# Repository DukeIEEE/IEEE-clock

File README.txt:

Analog LED clock

This is a project to create a programmable clock using LEDs to represent numbers and hand movements.

Contents:

AnalogClock - Arduino code
Designs - Clock designs for laser cutting
Schematics - PCB schematics and boards
Proposal - Contains a timeline for this workshop
Documents - Contains BOM and datasheets

Programming using arduino-1.0.1 and Arduino UNO programmer:

Place atmega into programmer
Connect all wires except reset to PCB
Upload ArduinoISP -- UNO, Arduino as ISP
Burn bootloader -- Arduino328, Arduino as ISP

Remove atmega from programmer
Connect reset wire
Run a sketch -- Arduino328, AVRISP mkII

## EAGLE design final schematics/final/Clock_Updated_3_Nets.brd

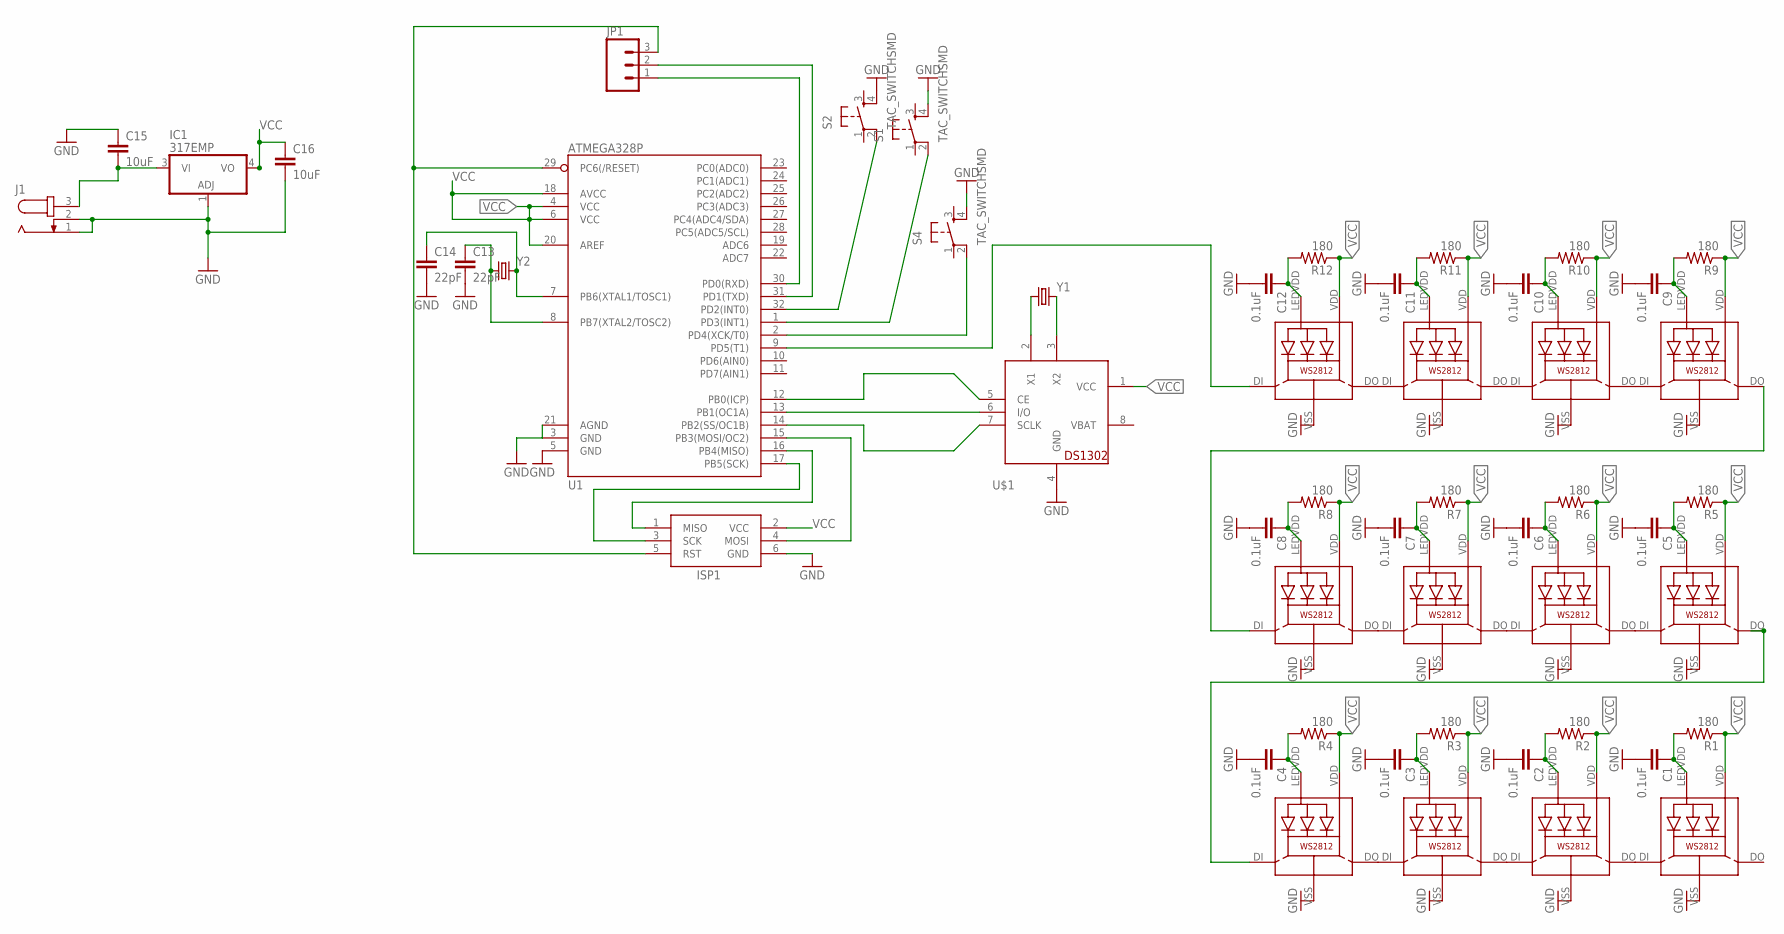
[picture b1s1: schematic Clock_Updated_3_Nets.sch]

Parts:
C1, C2, C3, C4, C5, C6, C7, C8, C9, C10, C11, C12: 0.1uF; 0603-CAP
C13, C14: 22pF; 0603-CAP
C15, C16: 10uF; 1206
IC1: 317EMP; SOT223
ISP1: AVRISP-6; AVRISP
J1: JACK-PLUG0; SPC4077
JP1: M03JST-PTH-VERT; JST-3-PTH-VERT
LED1, LED2, LED3, LED4, LED5, LED6, LED7, LED8, LED9, LED10, LED11, LED12: WS2812
R1, R2, R3, R4, R5, R6, R7, R8, R9, R10, R11, R12: 180; 0603-RES
S1, S2, S4: TAC_SWITCHSMD; TACTILE-SWITCH-SMD
U1: ATMEGA328P; TQFP32-08
U$1: DS1302; DIL08-ROUND
Y1: CRYSTALTC38H; TC38H
Y2: CRYSTALSMD; HC49UP

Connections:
GND: C1.2, C2.2, C3.2, C4.2, C5.2, C6.2, C7.2, C8.2, C9.2, C10.2, C11.2, C12.2, C13.2, C14.2, C15.1, C16.2, IC1.1 (ADJ), ISP1.6 (GND), J1.1, J1.2, LED1.VSS (GND), LED2.VSS (GND), LED3.VSS (GND), LED4.VSS (GND), LED5.VSS (GND), LED6.VSS (GND), LED7.VSS (GND), LED8.VSS (GND), LED9.VSS (GND), LED10.VSS (GND), LED11.VSS (GND), LED12.VSS (GND), S1.4, S2.4, S4.4, U1.3 (GND), U1.5 (GND), U1.21 (AGND), U$1.4 (GND)
unnamed: ISP1.4 (MOSI), U1.15 (PB3(MOSI/OC2))
unnamed: ISP1.1 (MISO), U1.16 (PB4(MISO))
unnamed: JP1.1, U1.30 (PD0(RXD))
unnamed: S2.2, U1.32 (PD2(INT0))
unnamed: U$1.3 (X2), Y1.2
unnamed: U$1.2 (X1), Y1.1
unnamed: C1.1, LED1.LEDVDD, R1.2
unnamed: C2.1, LED2.LEDVDD, R2.2
unnamed: LED1.DI, LED2.DO
unnamed: C3.1, LED3.LEDVDD, R3.2
unnamed: C4.1, LED4.LEDVDD, R4.2
unnamed: LED3.DI, LED4.DO
unnamed: C5.1, LED5.LEDVDD, R5.2
unnamed: C6.1, LED6.LEDVDD, R6.2
unnamed: LED5.DI, LED6.DO
unnamed: C7.1, LED7.LEDVDD, R7.2
unnamed: C8.1, LED8.LEDVDD, R8.2
unnamed: LED7.DI, LED8.DO
unnamed: C9.1, LED9.LEDVDD, R9.2
unnamed: C10.1, LED10.LEDVDD, R10.2
unnamed: LED9.DI, LED10.DO
unnamed: C11.1, LED11.LEDVDD, R11.2
unnamed: C12.1, LED12.LEDVDD, R12.2
unnamed: LED11.DI, LED12.DO
unnamed: LED4.DI, LED5.DO
unnamed: LED8.DI, LED9.DO
unnamed: JP1.2, U1.31 (PD1(TXD))
unnamed: S1.2, U1.1 (PD3(INT1))
unnamed: U1.13 (PB1(OC1A)), U$1.6 (I/O)
unnamed: U1.12 (PB0(ICP)), U$1.5 (CE)
unnamed: U1.14 (PB2(SS/OC1B)), U$1.7 (SCLK)
unnamed: ISP1.3 (SCK), U1.17 (PB5(SCK))
unnamed: ISP1.5 (RST), JP1.3, U1.29 (PC6(/RESET))
unnamed: S4.2, U1.2 (PD4(XCK/T0))
unnamed: C13.1, U1.8 (PB7(XTAL2/TOSC2)), Y2.1
unnamed: LED2.DI, LED3.DO
unnamed: LED6.DI, LED7.DO
unnamed: LED10.DI, LED11.DO
unnamed: LED12.DI, U1.9 (PD5(T1))
unnamed: C14.1, U1.7 (PB6(XTAL1/TOSC1)), Y2.2
unnamed: C15.2, IC1.3 (VI), J1.3
VBAT: U$1.8 (VBAT)
VCC: C16.1, IC1.4 (VO), ISP1.2 (VCC), LED1.VDD, LED2.VDD, LED3.VDD, LED4.VDD, LED5.VDD, LED6.VDD, LED7.VDD, LED8.VDD, LED9.VDD, LED10.VDD, LED11.VDD, LED12.VDD, R1.1, R2.1, R3.1, R4.1, R5.1, R6.1, R7.1, R8.1, R9.1, R10.1, R11.1, R12.1, U1.4 (VCC), U1.6 (VCC), U1.18 (AVCC), U1.20 (AREF), U$1.1 (VCC)

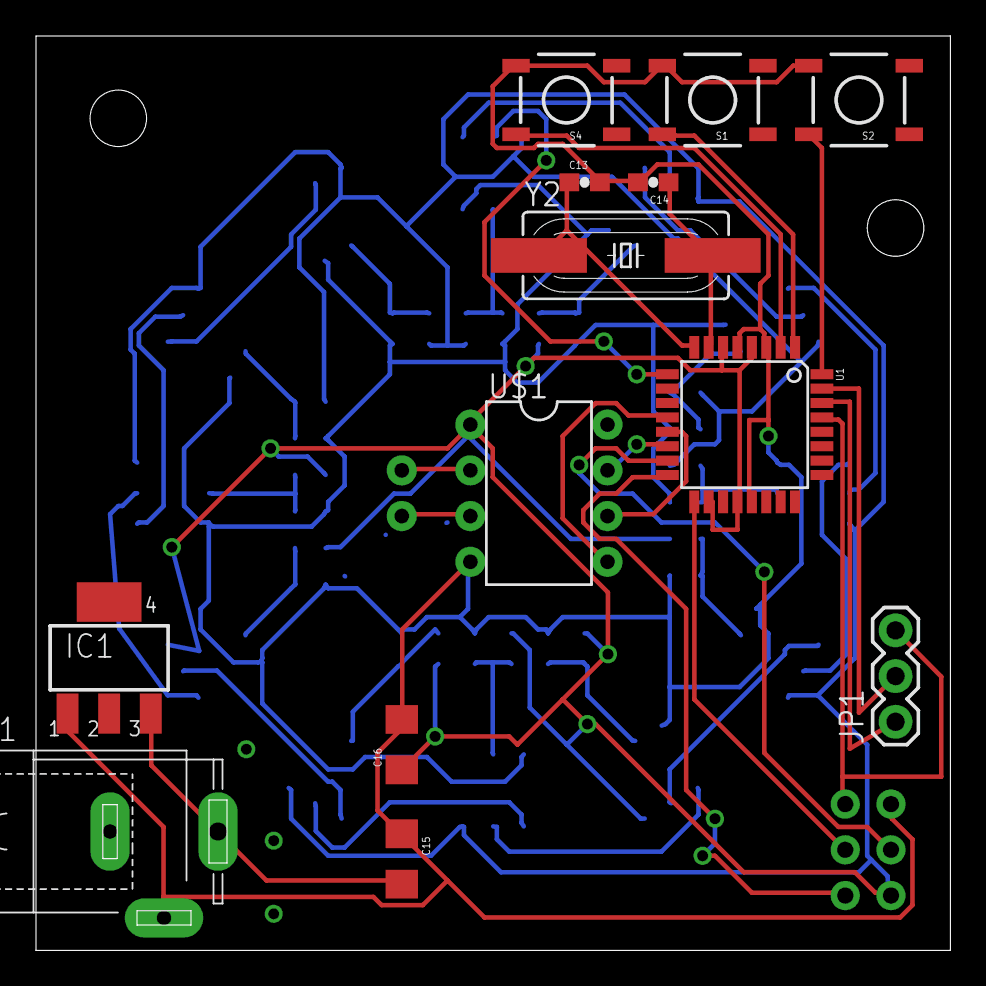
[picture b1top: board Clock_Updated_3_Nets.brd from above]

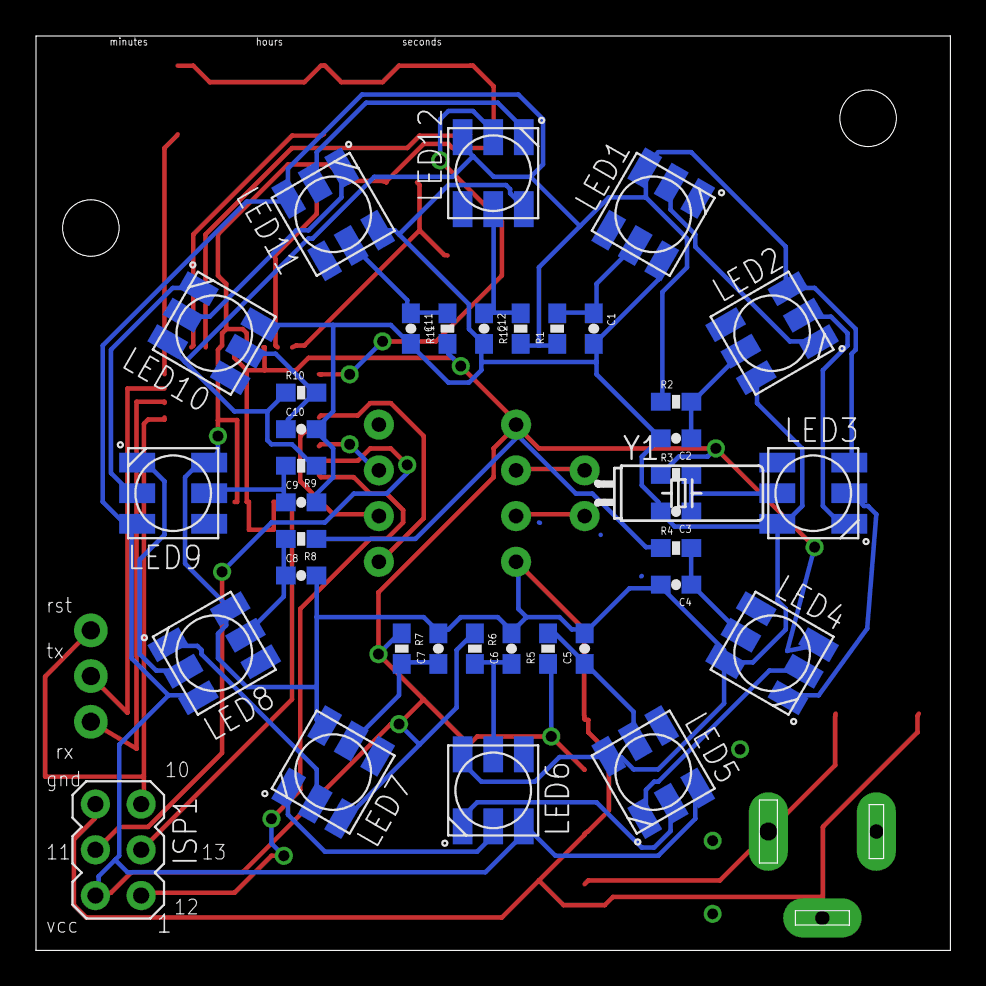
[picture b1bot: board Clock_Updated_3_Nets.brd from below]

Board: 2 copper layers, 50.8 x 50.8 mm, 51 parts (38 on the bottom side), 43 nets.

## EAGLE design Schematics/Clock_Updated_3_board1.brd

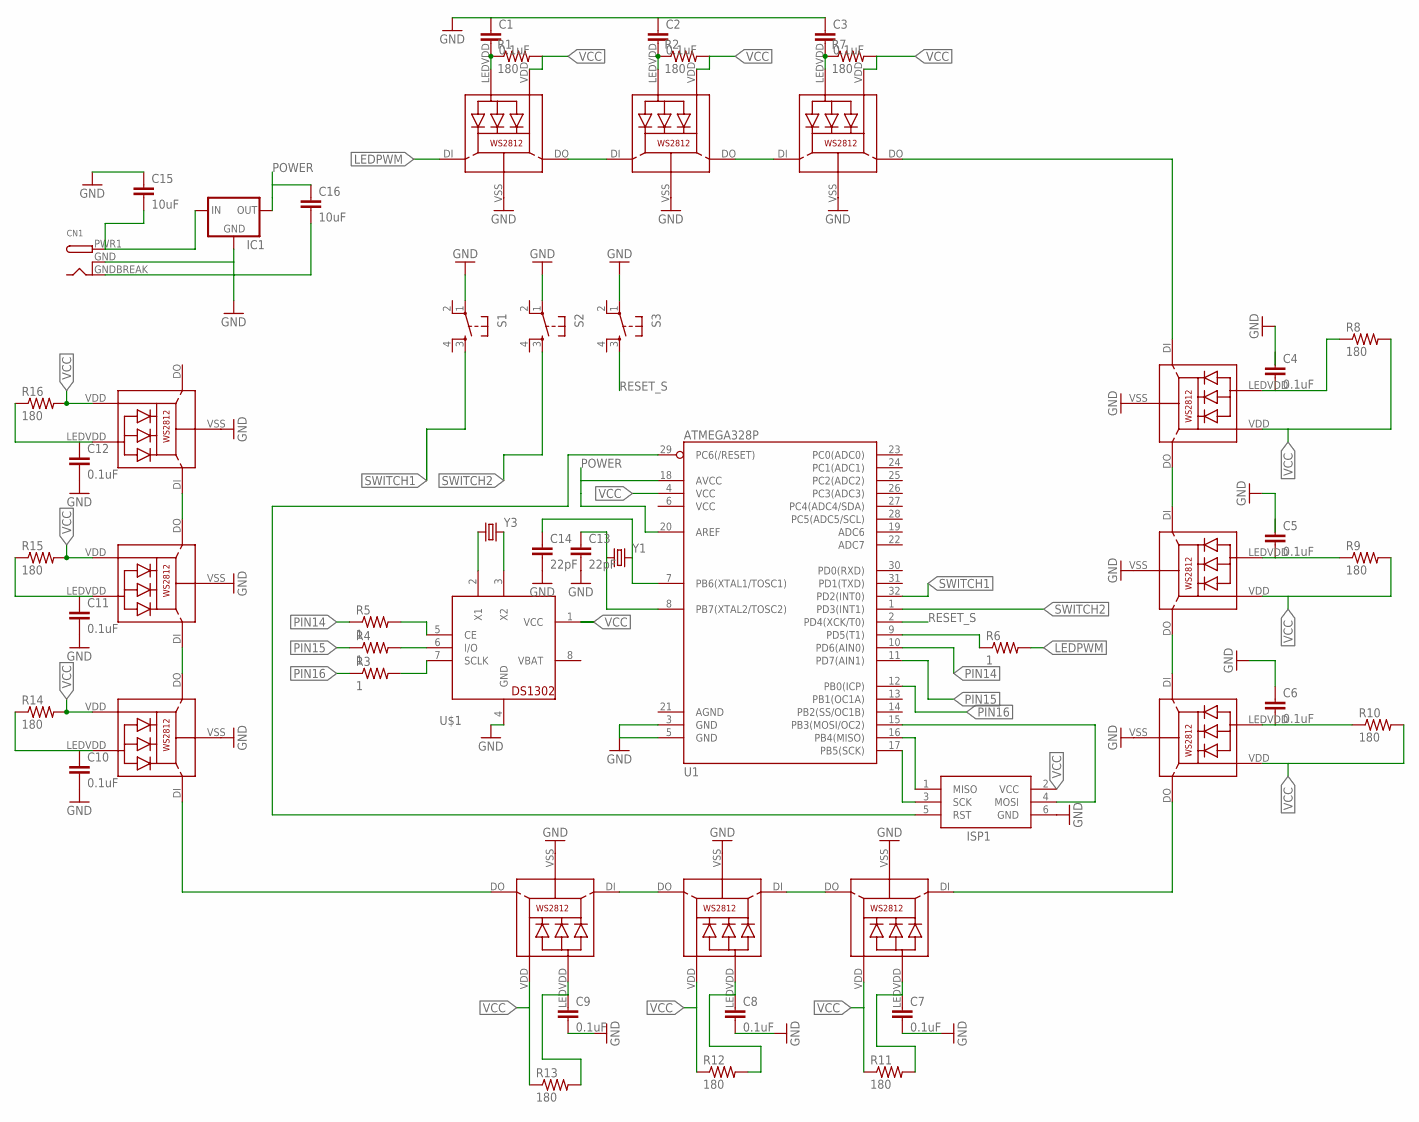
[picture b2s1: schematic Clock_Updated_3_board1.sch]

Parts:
C1, C2, C3, C4, C5, C6, C7, C8, C9, C10, C11, C12: 0.1uF; 0603-CAP
C13, C14: 22pF; 0603-CAP
C15, C16: 10uF; 1206
CN1: DCBARRELSMT; DCJACK_2MM_SMT
IC1: V_REG_78XX-TO-220; TO-220-ALT
ISP1: AVRISP-6; AVRISP
LED1, LED2, LED3, LED4, LED5, LED6, LED7, LED8, LED9, LED10, LED11, LED12: WS2812
R1, R2, R7, R8, R9, R10, R11, R12, R13, R14, R15, R16: 180; 0603-RES
R3, R4, R5, R6: 1; 0603-RES
S1, S2, S3: TAC_SWITCHPTH; TACTILE-PTH
U1: ATMEGA328P; TQFP32-08
U$1: DS1302; DIL08-ROUND
Y1: CRYSTALSMD; HC49UP
Y3: CRYSTAL32-SMD; CRYSTAL-32KHZ-SMD

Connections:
LEDPWM: LED1.DI, R6.2
unnamed: R6.1, U1.9 (PD5(T1))
unnamed: C4.2, LED5.LEDVDD, R8.1
unnamed: C5.2, LED6.LEDVDD, R9.1
unnamed: C6.2, LED7.LEDVDD, R10.1
unnamed: LED9.DO, LED10.DI
unnamed: LED10.DO, LED11.DI
unnamed: U$1.3 (X2), Y3.X2 (2)
unnamed: U$1.2 (X1), Y3.X1 (1)
unnamed: R3.2, U$1.7 (SCLK)
unnamed: R4.2, U$1.6 (I/O)
unnamed: R5.2, U$1.5 (CE)
unnamed: LED4.DI, LED11.DO
unnamed: LED6.VDD, R9.2
unnamed: LED8.DO, LED12.DI
unnamed: C7.1, LED9.LEDVDD, R11.2
unnamed: LED6.DO, LED7.DI
unnamed: LED3.DO, LED5.DI
unnamed: LED5.DO, LED6.DI
unnamed: LED1.DO, LED2.DI
unnamed: LED2.DO, LED3.DI
unnamed: C8.1, LED10.LEDVDD
unnamed: LED4.DO, LED8.DI
unnamed: C9.1, LED11.LEDVDD, R13.2
unnamed: LED12.LEDVDD, R16.1
unnamed: LED7.DO, LED9.DI
unnamed: LED4.LEDVDD, R14.1
unnamed: ISP1.4 (MOSI), U1.15 (PB3(MOSI/OC2))
unnamed: LED8.LEDVDD, R15.1
unnamed: C1.2, LED1.LEDVDD, R1.1
unnamed: C2.2, LED2.LEDVDD, R2.1
unnamed: C3.2, LED3.LEDVDD, R7.1
unnamed: ISP1.1 (MISO), U1.16 (PB4(MISO))
unnamed: ISP1.3 (SCK), U1.17 (PB5(SCK))
unnamed: ISP1.5 (RST), U1.29 (PC6(/RESET))
unnamed: C15.2, CN1.PWR1 (PWR), IC1.IN
unnamed: C13.1, U1.8 (PB7(XTAL2/TOSC2)), Y1.1
unnamed: C14.1, U1.7 (PB6(XTAL1/TOSC1)), Y1.2
PIN14: R5.1, U1.10 (PD6(AIN0))
PIN15: R4.1, U1.11 (PD7(AIN1))
PIN16: R3.1, U1.12 (PB0(ICP))
POWER: C16.1, IC1.OUT, U1.18 (AVCC), U1.20 (AREF)
RESET_S: S3.3, U1.2 (PD4(XCK/T0))
SWITCH1: S1.3, U1.32 (PD2(INT0))
SWITCH2: S2.3, U1.1 (PD3(INT1))
VBAT: U$1.8 (VBAT)
VCC: ISP1.2 (VCC), LED1.VDD, LED2.VDD, LED3.VDD, LED4.VDD, LED5.VDD, LED7.VDD, LED8.VDD, LED9.VDD, LED10.VDD, LED11.VDD, LED12.VDD, R8.2, R10.2, R11.1, R12.1, R13.1, R14.2, R15.2, R16.2, U1.4 (VCC), U$1.1 (VCC)

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
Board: 2 copper layers, 54 parts (0 on the bottom side), 47 nets, no tracks yet.

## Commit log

2014-09-21 initial
    a
2014-09-22 Added README
2014-09-27 Added basic design template
2014-10-04 added schematic
2014-10-11 Updated design to have frosted triangle regions, screw holes
2014-10-14 buttons work now, see comments
2014-10-18 added example designs and updated PCB schematic
2014-10-18 organized documents into one folder
2014-10-18 changed seconds to have gradual fading in/out
2014-10-25 Added two Duke designs
2014-10-25 Added basic stand design
2014-10-25 line color change
2014-10-25 changed h,m,sec hands to use 12 LEDs on the strip instead of the entire strip in preparation for the code for the actual clock
2014-10-25 added fade in/out for hour and minute 'hands'
2014-10-27 fixed 'vibrations' bug with buttons
2014-10-31 rewired buttons without resistors, using INPUT_PULLUP; added a reset button for the second hand
2014-11-01 fixed button indexing issue (only uses 12 LEDs now instead of 13)
2014-11-01 fixed buttons conflicting with time keeping
2014-11-01 plays a rainbow animation at every hour
2014-11-03 updated schematics, will work on hourly blue LED transitional gradient, will change button delay later
2014-11-08 changed seconds reset button into a brightness setting button
2015-01-24 found out vdd and ledvdd were switched
2015-01-24 changed wires
2015-01-31 switched LEDs clock direction to go from 11 -> 0 rather than 0 -> 11 because LEDs are indexed in CCW direction on circuit board
2015-02-17 added test files
2015-02-17 changed clock pins
2015-02-17 fixed seconds hand scaling problem
2015-02-17 attempted to fix minute hand color scaling problem when pressing the minutes button
2015-02-21 changed stand
2015-04-22 added designs to be laser-cut
2015-11-21 fixed clock direction bug after reverting to Nov-8-2014 commit

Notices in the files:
parts and their libraries:
SparkFun-FreqCtrl: Licensing: Creative Commons ShareAlike 4.0 International - https://creativecommons.org/licenses/by-sa/4.0
